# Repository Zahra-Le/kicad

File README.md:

# kicad
Just for test
Hi how is it going? :)
just a test

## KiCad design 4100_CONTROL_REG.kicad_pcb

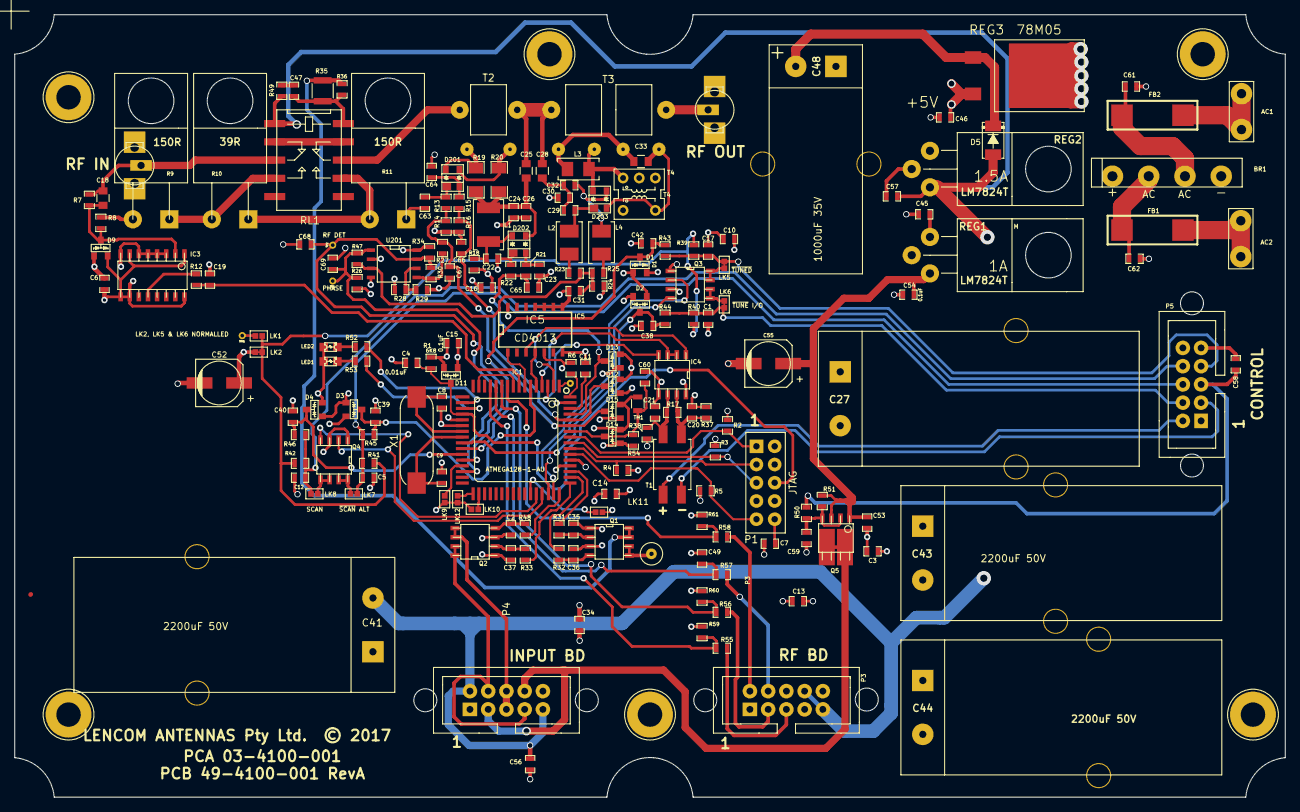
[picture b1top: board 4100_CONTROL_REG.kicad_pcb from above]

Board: 4 copper layers, 177.0 x 109.0 mm, 193 parts (0 on the bottom side), 114 nets.

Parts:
BR1: Vishay GBL01-E3/51; VISHAY_BRIDGE_GB301-E3-51
C1, C3, C5, C6, C7, C10, C11, C12, C13, C14, C15, C16, C17, C22, C34, C38, C39, C40, C42, C46, C47, C53, C54, C56, C57, C58, C59, C60, C65, C66, C67, C69: 0.1uF; SM0603_Capa
C2, C31, C35, C36, C37, C61, C62: .01uF; SM0603_Capa
C4, C23, C63, C64: 0.01uF; SM0603_Capa
C8, C9: 15pF; SM0603_Capa
C18: 3.3pF 200V; C_0805
C19, C30: 47pF; SM0603_Capa
C20, C21: 100pF; SM0603_Capa
C24: 39pF; SM0603_Capa
C25, C28: 4.7pF 200V; C_0805
C26: 1.8pF; SM0603_Capa
C27, C41, C44: 2200uF 50V; Cap_Electro_18X35_Horiz_7.5_L
C29, C32: 68nF; SM0603_Capa
C33: 390pF 200V; C_0805
C43: 2200uF 50V; Cap_Electro_18X35_Horiz_7.5_R
C45: .1uF; SM0603_Capa
C48: 1000uF 35V; Cap_Electro_13X27_Horiz_5.5_L
C49: 1nF; SM0603_Capa
C52: 22uF; CAP_ELECTRO_22uF_SMD
C55: 22uF 35V; C_ELECTRO_SM_LENCOM_40??_6.3x5.8
C68: 0F; SM0603_Capa
D1, D2, D3, D4, D9, D11, D12, D13, D14, D15: BAV99; BAV99L_ON_SEMI
D5: CD214A-B340LF; DIODE_CD214A-B340LF
D201, D202, D203: BAS70; sot143c
FB1, FB2: FB23_SMALL; FERRITE_BEAD_8.5X3mm
IC1: ATMEGA128-1-AU; ATmega64_L_14mm
IC3: 74AS161D; SO-16_W
IC4: SP483; so-8
IC5: CD4013; SO14N
L1: 1mH; Inductor_1mH
L2, L4: 100uH; Inductor_100uH
L3: 1uH; Inductor_1uH
LED1, LED2: E14 855-4641; LED_HSMH-C190_R
LK1, LK2, LK5, LK6, LK8, LK9, LK10, LK11, LK12: LINK_BRIDGE; JUMPER_2
LK7: LK7; JUMPER_2
NU1: Phase; PadVia1mm_0.5mm
P1: JTAG; Connect_5X2_0.1in
P3, P4, P5: RIBBON_BOX_PLUG_5_X_2; Connector_RIBBON_P_10p
Q1, Q2, Q3, Q4: SI4936ADY; so-8
Q5: SI4909DY; SO-8_LittleFoot
R1, R14, R16, R18, R22: 6K8; SM0603_Resistor
R2, R3, R4, R5, R7, R26, R34, R39, R40, R41, R42, R43, R44, R45, R46, R50, R51, R59, R60, R61: 10K; SM0603_Resistor
R6, R31, R32, R33, R48, R49: 10R; SM0603_Resistor
R8, R23, R24, R25, R27: 100K; SM0603_Resistor
R9, R11: 150R; TO220-R
R10: 39R; TO220-R
R12: 47R; SM0603_Resistor
R13, R15, R21, R28: 15K; SM0603_Resistor
R17: 110R; SM0603_Resistor
R19, R20: 100R 0.25W; SM1206
R29: 680; SM0603_Resistor
R30, R47: 10M; SM0603_Resistor
R35: 1K .5W; R_1210
R36: O/C; SM0603_Resistor
R37, R38: 600; SM0603_Resistor
R52, R53: 1K; SM0603_Resistor
R54: 27K; SM0603_Resistor
R55, R56, R57, R58: 0R; SM0603_Resistor
REG1, REG2: LM7824T; LM78XX_TO220_THROUGH_BOARD_MOUNT_R
REG3: 78M05; DPAK3_78M05
RL1: TQ2SL_LENCOMB; TQ2_RELAY_LENCOM
SK1, SK2: COAX_SKT; TMP_Connector_LGE_GND
SP1, SP2: SPADE_TERMINAL; Spade_Term_PCB_5mm
T1: CM04RC; CMChokeCM04RC
T2: 47-1001-001; TFMR_47-1001-001
T3: 47-1002-001; TFMR_47-1002-001
T4: 47-1003-001
TH1: THERMISTOR; R_0805
TP1: Phase; PadVia1mm_0.5mm
TP2: RF Detect; PadVia1mm_0.5mm
U201: LM393; SO8N
W1: PadVia100
X1: 14.7456MHz; CRYSTAL_A_Sml

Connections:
/485 Data+: P5.2, T1.3
/485 Data-: P5.3, T1.4
/485TX: IC1.4, IC4.2, IC4.3
/+24B: C53.2, C54.1, C55.1, Q5.1, Q5.3, R51.2, REG1.3
/+24V: C41.1, C56.2, C57.1, D5.2, P3.8, P3.9, P4.2, P4.9, R49.1, REG2.3, RL1.1
/+24V ALT ANT: P4.3, P4.8, Q5.5, Q5.6, Q5.7, Q5.8
/ALT ANT SELECT: IC1.49, R33.1
/AUX Ant: P4.4, P4.7, Q2.7, Q2.8
/Arm: IC1.5, IC5.4
/CLOCK: IC1.11, R56.2, R60.1
/DATA: C49.2, IC1.12, R57.2
/Frequency: C19.1, IC1.8, R12.2
/IN1: C38.1, D2.3, IC1.25, R44.1
/IN2: C42.1, D1.3, IC1.26, R43.1
/IN3: C40.1, D4.3, IC1.27, R46.1
/IN4: C39.1, D3.3, IC1.6, R45.1
/LED1: IC1.19, R53.2
/LED2: IC1.18, R52.2
/NU: LK1.2, NU1.1
/O/P_En: IC1.13, R55.2, R59.1
/OC1A: IC1.9, IC1.15
/OUT1: IC1.46, Q3.4
/OUT2: IC1.47, Q3.2
/OUT3: IC1.44, Q4.4
/OUT4: IC1.45, Q4.2
/PULL UP: LK1.1, LK2.1, R39.1, R40.1, R41.1, R42.1
/Pad: IC1.51, R31.1
/Phase: C69.1, IC1.30, R26.2, R47.2, TP1.1, U201.1
/RFDetect: C68.1, IC1.28, R30.2, R34.2, TP2.1, U201.7
/RxD0: IC1.2, IC4.1, IC5.3
/STROBE: IC1.10, R58.2, R61.2
/Serial Int: IC1.7, IC5.1
/Spare OP: IC1.50, R32.1
/TCK: IC1.57, P1.1, R2.2
/TDI: IC1.54, P1.9, R5.2
/TDO: IC1.55, P1.3, R4.2
/TMS: IC1.56, P1.5, R3.2
/TUNE: IC1.48, R48.1
/TUNE OC: P4.5, P4.6, Q2.5, Q2.6
/Temperature: C60.1, D14.3, IC1.58, R54.2, TH1.2
/TxD0: IC1.3, IC4.4
/VCC: C3.1, C6.1, C7.1, C10.1, C13.1, C14.1, C15.1, C16.1, C34.1, C46.1, C52.1, D1.2, D2.2, D3.2, D4.2, D9.2, D11.2, D12.2, D13.2, D14.2, D15.2, IC1.21, IC1.52, IC3.1, IC3.7, IC3.9, IC3.10, IC3.16, IC4.8, IC5.5, IC5.14, LED1.2, LED2.2, LK2.2, P1.4, P1.7, P3.7, R1.1, R2.1, R3.1, R4.1, R5.1, R6.1, R18.1, R26.1, R28.1, R34.1, R38.1, REG3.3, TH1.1, U201.8
/Vfwd: C67.2, D15.3, IC1.59, R13.2, R14.1, R27.1
/Vref: C66.2, D12.3, IC1.60, R15.2, R16.1
/Vsamp: C65.2, D13.3, IC1.61, R21.2, R22.1
/~ALT ANT +24 ON: C58.1, P5.5, R50.2
/~OUT1: LK6.2, Q3.5, Q3.6
/~OUT2: LK5.2, Q3.7, Q3.8
/~OUT3: LK8.2, Q4.5, Q4.6
/~OUT4: LK7.2, Q4.7, Q4.8
/~RESET: C4.1, D11.3, IC1.20, P1.6, R1.2
/~SCAN: C12.2, LK8.1, P5.8, R42.2, R46.2
/~SCAN ALT ANT: C5.2, LK7.1, P5.6, R41.2, R45.2
/~Spare OP: Q1.5, Q1.6, W1.1
/~TUNE: C1.2, LK6.1, P5.4, R40.2, R44.2
/~TUNED: C17.2, LK5.1, P5.7, R39.2, R43.2
GND: BR1.1, C1.1, C2.2, C3.2, C4.2, C5.1, C6.2, C7.2, C8.1, C9.1, C10.2, C11.1, C12.1, C13.2, C14.2, C15.2, C16.2, C17.1, C19.2, C20.2, C21.2, C22.2, C23.2, C24.2, C26.2, C27.2, C30.2, C31.2, C34.2, C35.2, C36.2, C37.2, C38.2, C39.2, C40.2, C41.2, C42.2, C43.2, C44.2, C45.2, C46.2, C48.2, C49.1, C52.2, C53.1, C54.2, C55.2, C56.1, C57.2, C58.2, C59.2, C60.2, C61.2, C62.2, C63.2, C64.1, C65.1, C66.1, C67.1, C68.2, C69.2, D1.1, D2.1, D3.1, D4.1, D9.1, D11.1, D12.1, D13.1, D14.1, D15.1, D202.1, IC1.22, IC1.53, IC1.63, IC3.3, IC3.4, IC3.5, IC3.6, IC3.8, IC4.5, IC5.7, IC5.8, IC5.9, IC5.10, IC5.11, LK9.2, LK10.2, LK11.1, LK12.1, P1.2, P1.10, P3.1, P3.6, P3.10, P4.1, P4.10, P5.1, P5.9, P5.10, Q1.1, Q1.3, Q2.1, Q2.3, Q3.1, Q3.3, Q4.1, Q4.3, R8.2, R9.2, R11.1, R14.2, R16.2, R22.2, R24.2, R29.2, R37.1, R54.1, R59.2, R60.2, R61.1, REG1.2, REG2.2, REG3.2, SK1.2, SK2.2, T4.2, T4.3, U201.2, U201.4
unnamed: BR1.2, C61.1, FB2.2
unnamed: BR1.3, C27.1, C43.1, C44.1, C45.1, REG1.1, REG2.1
unnamed: BR1.4, C62.1, FB1.2
unnamed: C2.1, Q2.4, R48.2
unnamed: C8.2, IC1.23, X1.2
unnamed: C9.2, IC1.24, X1.1
unnamed: C11.2, IC1.62
unnamed: C18.1, R7.1, RL1.3, SK1.1
unnamed: C18.2, D9.3, IC3.2, R7.2, R8.1
unnamed: C20.1, IC4.7, R17.1, R37.2, T1.1
unnamed: C21.1, IC4.6, R17.2, R38.2, T1.2
unnamed: C22.1, D202.4, L1.2, R18.2
unnamed: C23.1, D202.2, R21.1
unnamed: C24.1, C25.2, C26.1, D202.3, L1.1, R19.2, R20.2
unnamed: C25.1, C28.1, T2.2, T3.1
unnamed: C28.2, C29.2, C30.1, C32.1
unnamed: C29.1, D203.1, L2.1
unnamed: C31.1, R23.2, R24.1, R25.1, R47.1, U201.3
unnamed: C32.2, D203.3, L4.1
unnamed: C33.1, L3.2, T3.3, T3.5
unnamed: C33.2, D203.2, T3.6, T4.4
unnamed: C35.1, Q1.2, R31.2
unnamed: C36.1, Q1.4, R32.2
unnamed: C37.1, Q2.2, R33.2
unnamed: C47.1, R35.1, R36.1, RL1.10
unnamed: C47.2, R49.2
unnamed: C48.1, D5.1, REG3.1
unnamed: C59.1, Q5.2, Q5.4, R50.1, R51.1
unnamed: C63.1, D201.1, R13.1
unnamed: C64.2, D201.2, R15.1
unnamed: D201.3, R20.1, T2.4
unnamed: D201.4, R19.1, T2.3
unnamed: D203.4, L3.1, T3.4, T4.1
unnamed: FB1.1, SP2.1
unnamed: FB2.1, SP1.1
unnamed: IC1.29, LK12.2
unnamed: IC1.33, LK9.1
unnamed: IC1.34, LK10.1
unnamed: IC1.43, LK11.2
unnamed: IC1.64, R6.2
unnamed: IC3.12, R12.1
unnamed: L2.2, R23.1
unnamed: L4.2, R25.2
unnamed: LED1.1, R53.1
unnamed: LED2.1, R52.1
unnamed: P3.2, R58.1
unnamed: P3.3, R56.1
unnamed: P3.4, R57.1
unnamed: P3.5, R55.1
unnamed: Q1.7, Q1.8, R35.2, R36.2
unnamed: R10.1, R11.2, RL1.7
unnamed: R9.1, R10.2, RL1.4
unnamed: R27.2, R30.1, U201.5
unnamed: R28.2, R29.1, U201.6
unnamed: RL1.2, RL1.9
unnamed: RL1.8, T2.1
unnamed: SK2.1, T3.2

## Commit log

2017-09-19 Create folder test

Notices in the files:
4100_CONTROL_REG.kicad_pcb:
LENCOM ANTENNAS Pty Ltd.  © 2017
